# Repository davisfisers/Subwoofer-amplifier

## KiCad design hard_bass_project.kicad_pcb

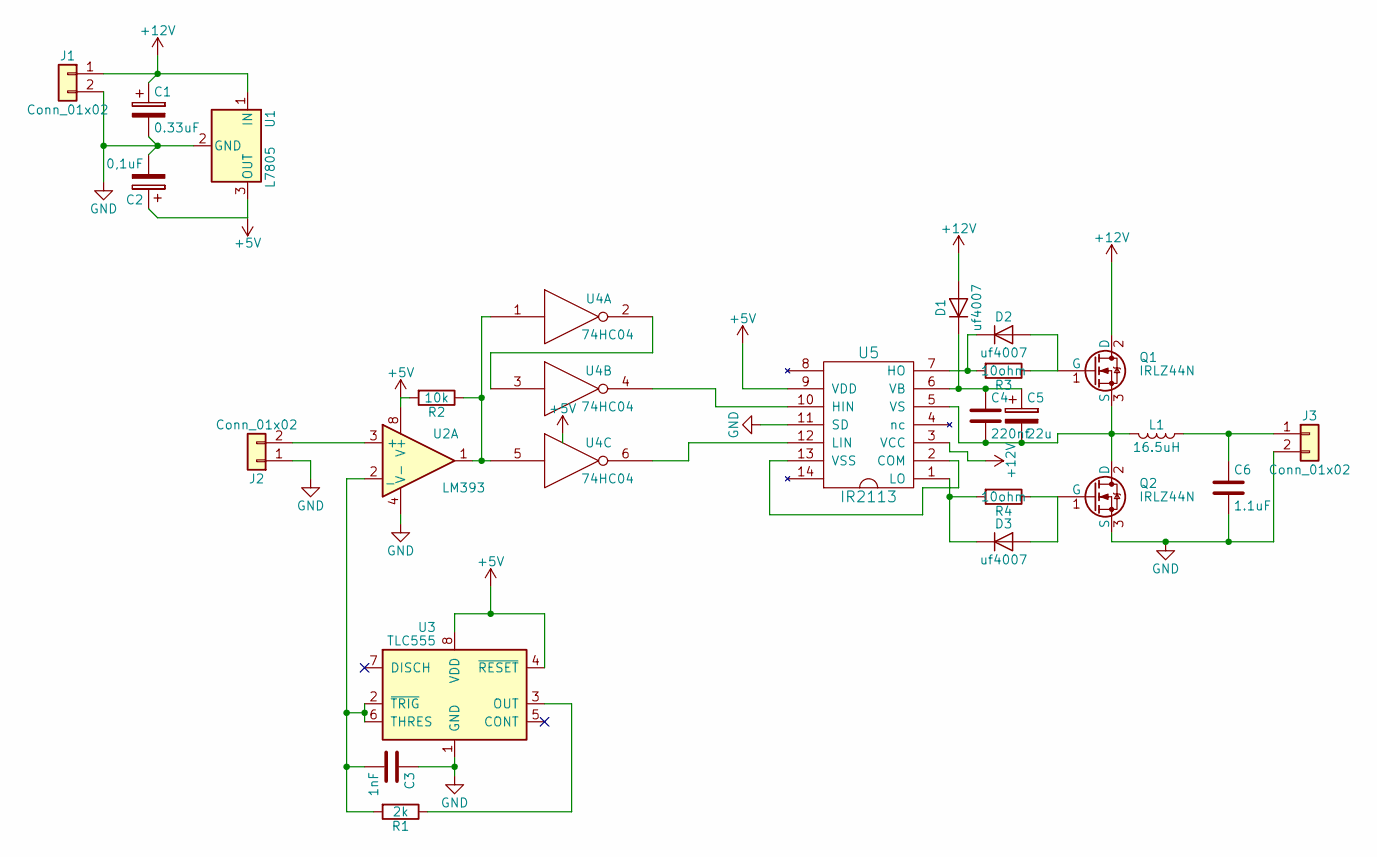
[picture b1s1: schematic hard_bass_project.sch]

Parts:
C1: 0.33uF; CP_Radial_D13.0mm_P5.00mm
C2: 0,1uF; C_Disc_D10.5mm_W5.0mm_P5.00mm
C3: 1nF; C_Disc_D6.0mm_W2.5mm_P5.00mm
C4: 220nf; C_Disc_D10.5mm_W5.0mm_P5.00mm
C5: 22u; CP_Radial_D14.0mm_P5.00mm
C6: 1.1uF; CP_Radial_D14.0mm_P5.00mm
D1, D2, D3: uf4007; D_A-405_P10.16mm_Horizontal
J1: Conn_01x02; TerminalBlock_Phoenix_MPT-2.54mm_2pol
J2, J3: Conn_01x02; Socket_Strip_Straight_1x02_Pitch2.54mm
L1: 16.5uH; L_Toroid_Vertical_L21.6mm_W11.4mm_P7.62mm_Pulse_KM-3
Q1, Q2: IRLZ44N; TO-220-3_Vertical
R1: 2k; R_Axial_DIN0207_L6.3mm_D2.5mm_P10.16mm_Horizontal
R2: 10k; R_Axial_DIN0207_L6.3mm_D2.5mm_P10.16mm_Horizontal
R3, R4: 10ohm; R_Axial_DIN0207_L6.3mm_D2.5mm_P10.16mm_Horizontal
U1: L7805; TO-220-3_Vertical
U2: LM393; DIP-8_W7.62mm_Socket
U3: TLC555; DIP-8_W7.62mm_Socket
U4: 74HC04; DIP-14_W7.62mm_Socket
U5: IR2113; DIP-14_W7.62mm_Socket

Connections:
+5V: C2.1, R2.2, U1.3 (OUT), U2.8 (V+), U3.4 (~RESET), U3.8 (VDD), U4.14 (VCC), U5.9 (VDD)
+12V: C1.1, D1.2 (A), J1.1, Q1.2 (D), U1.1 (IN), U5.3 (VCC)
GND: C1.2, C2.2, C3.1, C6.2, J1.2, J2.1, J3.2, Q2.3 (S), U1.2 (GND), U2.4 (V-), U3.1 (GND), U4.7 (GND), U5.11 (SD)
unnamed: C3.2, R1.2, U2.2 (_), U3.2 (~TRIG), U3.6 (THRES)
unnamed: C4.1, C5.1, D1.1 (K), U5.6 (VB)
unnamed: C4.2, C5.2, L1.2, Q1.3 (S), Q2.2 (D), U5.5 (VS)
unnamed: C6.1, J3.1, L1.1
unnamed: D2.1 (K), R3.2, U5.7 (HO)
unnamed: D2.2 (A), Q1.1 (G), R3.1
unnamed: D3.1 (K), R4.2, U5.1 (LO)
unnamed: D3.2 (A), Q2.1 (G), R4.1
unnamed: J2.2, U2.3 (+)
unnamed: R1.1, U3.3 (OUT)
unnamed: R2.1, U2.1, U4.1, U4.5
unnamed: U4.2, U4.3
unnamed: U4.4, U5.10 (HIN)
unnamed: U4.6, U5.12 (LIN)
unnamed: U5.2 (COM), U5.13 (VSS)

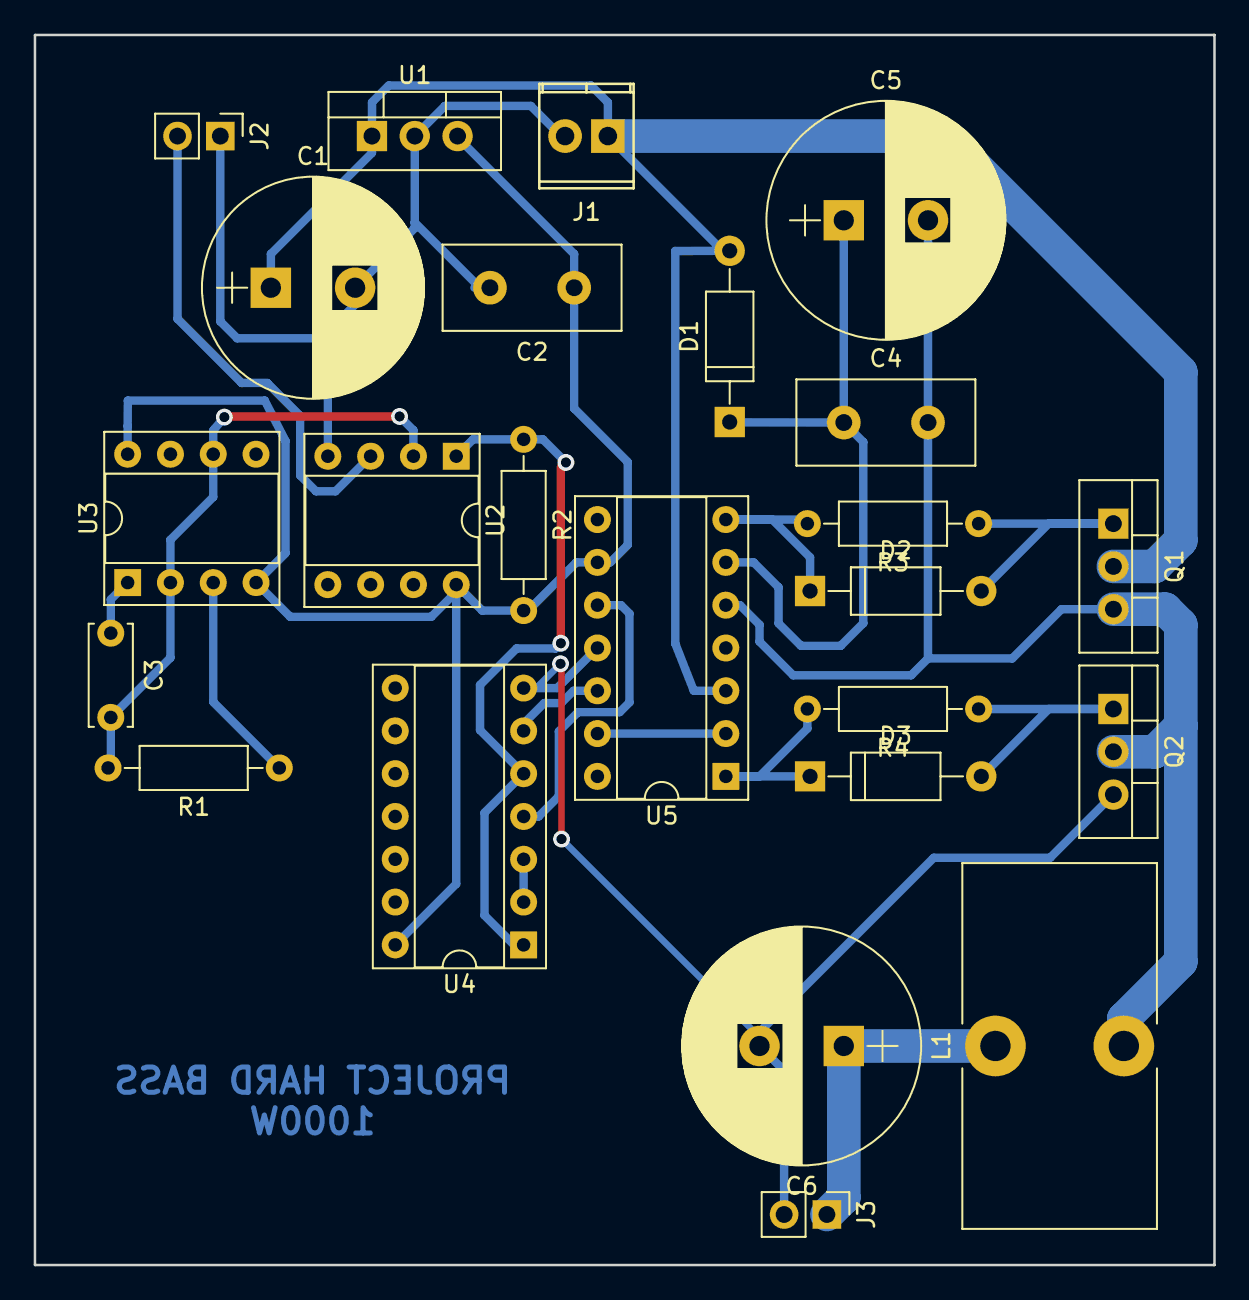
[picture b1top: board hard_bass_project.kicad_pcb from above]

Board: 2 copper layers, 70.0 x 73.0 mm, 24 parts (0 on the bottom side), 18 nets.

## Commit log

2019-03-23 upload
